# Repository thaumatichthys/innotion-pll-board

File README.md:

# ADF4158 + YSGM556006 Test Board  

**Thanks Mr GPT for (some parts of) the readme**

**5.5–6.0 GHz PLL/VCO Synthesizer w/ RP2040 Control**

This project is a small test board built around the **Analog Devices ADF4158** fractional-N PLL and the **Innotion YSGM556006** VCO module to generate RF signals in the **5.5–6.0 GHz** range.  
An **RP2040 microcontroller** drives the PLL over SPI, making it easy to test frequency sweeps, chirps, or single-tone synthesis.

## ✨ Features
- **ADF4158 PLL**
  - Fractional-N synthesizer  
  - Supports various shapes of ramps / chirps  

- **Innotion YSGM556006 VCO**
  - Very low cost VCO ($1.5/ea)
  - 5.5–6.0 GHz tuning range  
 
- **External (off-board) VCO Option**
  - SMA connectors expose VTUNE and VCO IN

- **RP2040 Controller**
  - Sends SPI commands for programming the PLL  
  - USB serial for sending commands / updating configs  

- **Other Board Components**
  - Loop filter for PLL stabilization  
  - Clean reference input stage (TCXO) 

## 📐 Purpose
This test board is designed for experimenting with PLL/VCO behavior at ~6 GHz.  
Typical use cases:

- Testing ADF4158 chirp/ramp features  
- Characterizing VCO tuning curve  
- LO generation for mixers or radar experiments  
- Measuring lock time, phase noise, loop stability  
- Learning / verifying SPI programming sequences for the ADF4158

## 🧠 How It Works
1. The **RP2040** boots and configures the ADF4158 via SPI.  
2. The ADF4158 sets the **divider ratio + ramp settings**.  
3. The loop filter drives the VCO’s **tuning voltage**, closing the PLL.  
4. The YSGM556006 outputs ~5.5–6 GHz RF.  
5. Lock status is monitored via **MUXOUT** exposed on the board.

## 🔌 SPI Interface (RP2040 → ADF4158)
- **MOSI** – PLL data input  
- **SCLK** – SPI clock  
- **LE** – Latch enable for register load  
- **MUXOUT** – Readable lock detect for debugging  

## ⚠️ Notes / Limitations
- The Innotion YSGM556006 is a very low cost ($1.5/ea) VCO, and has poor performance. This board was an attempt to test the feasibility of its use in a PLL.
- This test board is **not** a finalized RF product — it’s meant for bench characterization.  
- Ensure your RF chain and measurement equipment can safely handle 5–6 GHz at around 0 dBm.

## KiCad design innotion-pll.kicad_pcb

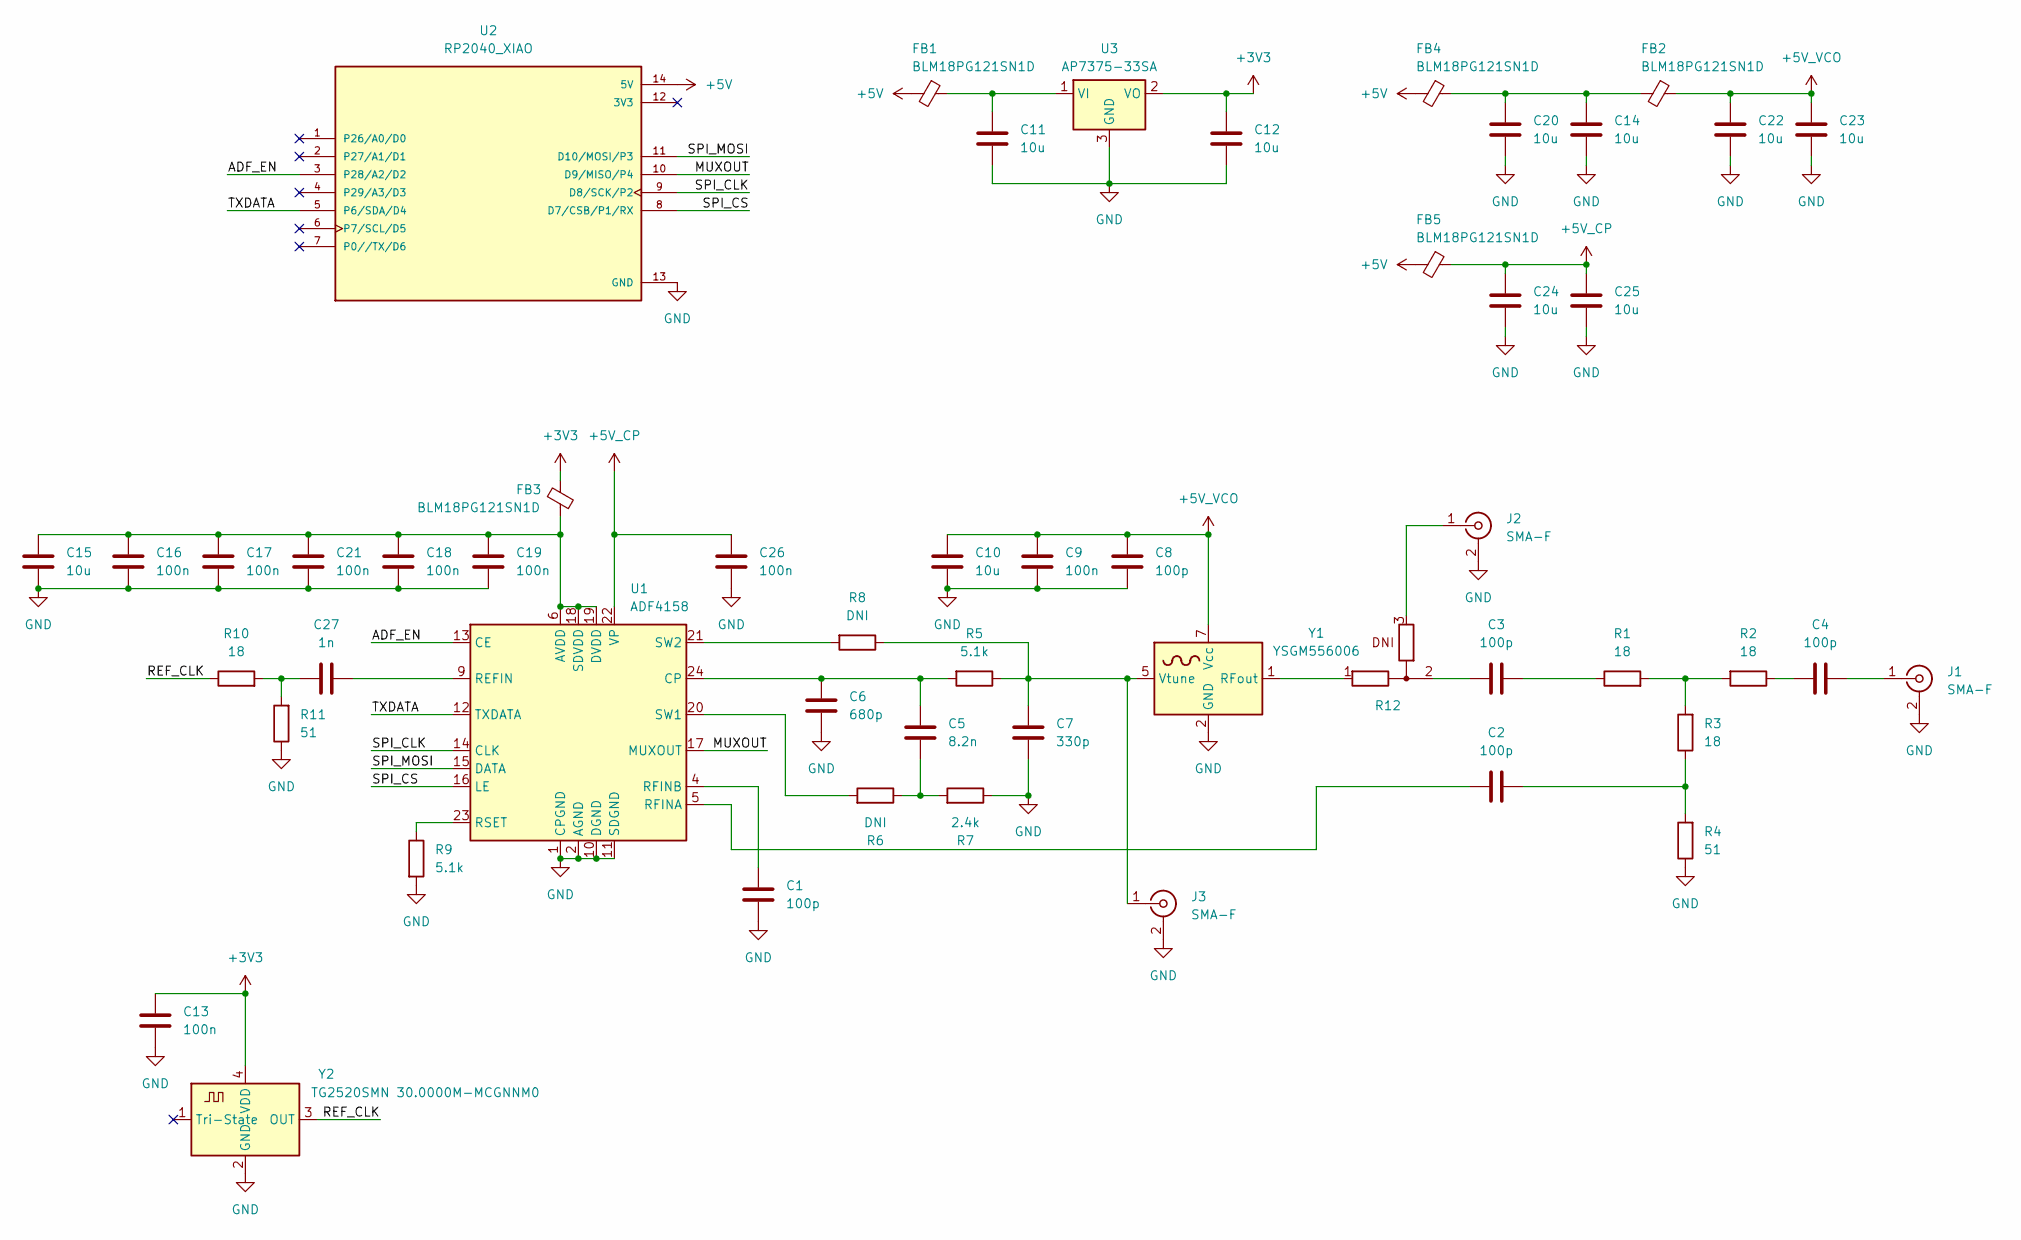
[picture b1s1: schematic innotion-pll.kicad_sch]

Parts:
C1, C2, C3, C4, C8: 100p; C_0402_1005Metric
C5: 8.2n; C_0402_1005Metric
C6: 680p; C_0402_1005Metric
C7: 330p; C_0402_1005Metric
C9, C13, C16, C17, C18, C19, C21, C26: 100n; C_0402_1005Metric
C10, C11, C12, C14, C15, C20, C22, C23, C24, C25: 10u; C_0805_2012Metric
C27: 1n; C_0402_1005Metric
FB1, FB2, FB3, FB4, FB5: BLM18PG121SN1D; L_0603_1608Metric_Pad1.05x0.95mm_HandSolder
J1, J2, J3: SMA-F; ADAMTECH_RF2-143-T-17-50-G
R1, R2, R3, R10: 18; R_0402_1005Metric
R4, R11: 51; R_0402_1005Metric
R5, R9: 5.1k; R_0402_1005Metric
R6, R8: DNI; R_0402_1005Metric
R7: 2.4k; R_0402_1005Metric
R12: R_0402_SELECT_MIRRORED
U1: ADF4158; LFCSP-24-1EP_4x4mm_P0.5mm_EP2.5x2.5mm
U2: RP2040_XIAO; MODULE_102010428; PARTREV 1.3
U3: AP7375-33SA; SOT-23
Y1: YSGM556006; INNOTION_VCO_MODULE_7x9mm
Y2: TG2520SMN 30.0000M-MCGNNM0; Oscillator_SMD_SeikoEpson_TG2520SMN-xxx-xxxxxx-4Pin_2.5x2.0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

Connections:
+3V3: C12.2, C13.2, FB3.1, U3.2 (VO), Y2.4 (VDD)
+5V: FB1.2, FB4.2, FB5.2, U2.14 (5V)
+5V_CP: C24.2, C25.2, C26.2, FB5.1, U1.22 (VP)
+5V_VCO: C8.2, C9.2, C10.2, C22.2, C23.2, FB2.1, Y1.7 (Vcc)
/ADF_EN: U1.13 (CE), U2.3 (P28/A2/D2)
/MUXOUT: U1.17 (MUXOUT), U2.10 (D9/MISO/P4)
/REF_CLK: R10.1, Y2.3 (OUT)
/SPI_CLK: U1.14 (CLK), U2.9 (D8/SCK/P2)
/SPI_CS: U1.16 (LE), U2.8 (D7/CSB/P1/RX)
/SPI_MOSI: U1.15 (DATA), U2.11 (D10/MOSI/P3)
/TXDATA: U1.12 (TXDATA), U2.5 (P6/SDA/D4)
GND: C1.1, C6.1, C7.1, C8.1, C9.1, C10.1, C11.1, C12.1, C13.1, C14.1, C15.1, C16.1, C17.1, C18.1, C19.1, C20.1, C21.1, C22.1, C23.1, C24.1, C25.1, C26.1, J1.2 (Ext), J2.2 (Ext), J3.2 (Ext), R4.1, R7.1, R9.2, R11.1, U1.1 (CPGND), U1.2 (AGND), U1.3 (AGND), U1.10 (DGND), U1.11 (SDGND), U1.25 (AGND), U2.13 (GND), U3.3 (GND), Y1.2 (GND), Y1.3 (GND), Y1.4 (GND), Y1.6 (GND), Y1.8 (GND), Y2.2 (GND)
unnamed: C2.2, R3.1, R4.2
unnamed: C3.1, R12.2
unnamed: C3.2, R1.1
unnamed: C4.1, R2.1
unnamed: C5.1, R6.1, R7.2
unnamed: C14.2, C20.2, FB2.2, FB4.1
unnamed: C27.2, R10.2, R11.2
unnamed: C4.2, J1.1 (In)
unnamed: J2.1 (In), R12.3
unnamed: C7.2, J3.1 (In), R5.1, R8.1, Y1.5 (Vtune)
unnamed: R1.2, R2.2, R3.2
unnamed: C5.2, C6.2, R5.2, U1.24 (CP)
unnamed: C15.2, C16.2, C17.2, C18.2, C19.2, C21.2, FB3.2, U1.6 (AVDD), U1.7 (AVDD), U1.8 (AVDD), U1.18 (SDVDD), U1.19 (DVDD)
unnamed: C27.1, U1.9 (REFIN)
unnamed: C2.1, U1.5 (RFINA)
unnamed: C1.2, U1.4 (RFINB)
unnamed: R9.1, U1.23 (RSET)
unnamed: R6.2, U1.20 (SW1)
unnamed: R8.2, U1.21 (SW2)
unnamed: C11.2, FB1.1, U3.1 (VI)
unnamed: R12.1, Y1.1 (RFout)

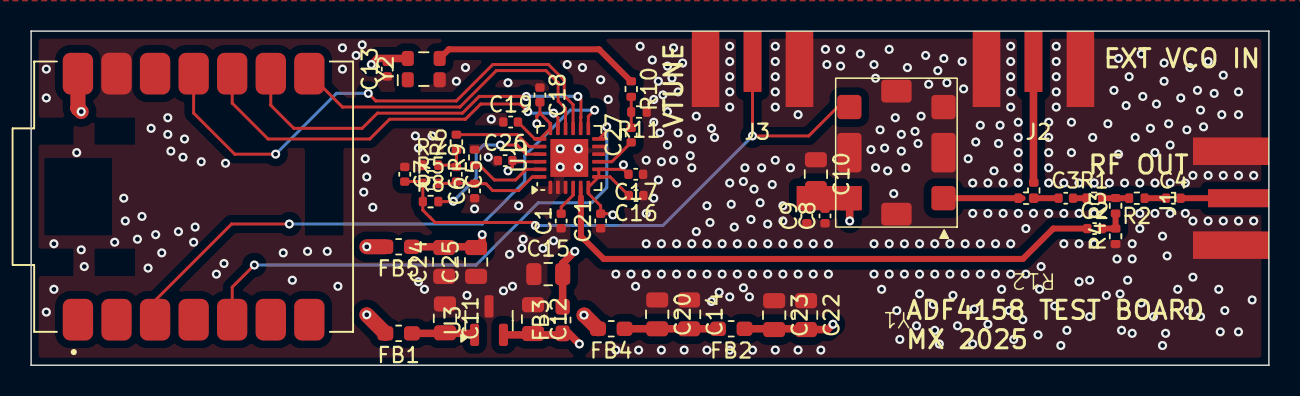
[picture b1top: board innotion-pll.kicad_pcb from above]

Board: 4 copper layers, 81.5 x 22.0 mm, 52 parts (0 on the bottom side), 33 nets.
